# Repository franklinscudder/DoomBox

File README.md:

# DoomBox
 An insane glitchy analog fuzz pedal designed for bass guitar.

## Progress

- Designed circuit and selected components on breadboard.
- Made a stripboard prototype, added a level knob and LED indicator.
- Designed PCB found herein with added power filtering (easily bypassed if it turns out to be useless).
- Waiting for the PCBs to arrive to test final assembly.

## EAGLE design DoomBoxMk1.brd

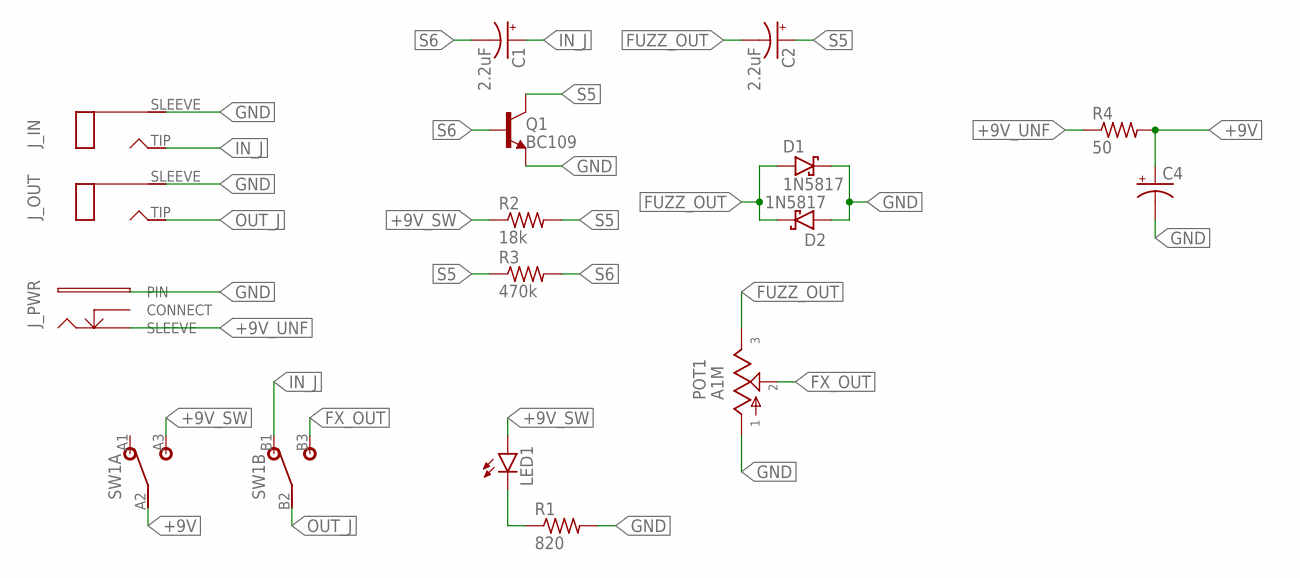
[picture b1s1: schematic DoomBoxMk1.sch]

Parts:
C1, C2: 2.2uF; 050_020_1
C4: 0802; 080_035_2
D1, D2: 1N5817; DO41-3
J_IN: MONO; MONO_JACK
J_OUT: MONO; MONO_JACK
J_PWR: DC; DC_POWER_JACK
LED1: LED5MM
POT1: A1M; 16MM-SQUARE
Q1: BC109; TO92-
R1: 820; R0207/3
R2: 18k; R0207/3
R3: 470k; R0207/3
R4: 50; R0207/3
SW1: DPDT

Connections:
+9V: C4.+, R4.2, SW1.A2 (2)
+9V_SW: LED1.A, R2.1, SW1.A3 (3)
+9V_UNF: J_PWR.SLEEVE, R4.1
FUZZ_OUT: C2.-, D1.A, D2.C, POT1.3
FX_OUT: POT1.2, SW1.B3 (3)
GND: C4.-, D1.C, D2.A, J_IN.SLEEVE, J_OUT.SLEEVE, J_PWR.PIN, POT1.1, Q1.1 (E), R1.2
IN_J: C1.+, J_IN.TIP, SW1.B1 (1)
unnamed: LED1.K (C), R1.1
OUT_J: J_OUT.TIP, SW1.B2 (2)
S5: C2.+, Q1.3 (C), R2.2, R3.1
S6: C1.-, Q1.2 (B), R3.2

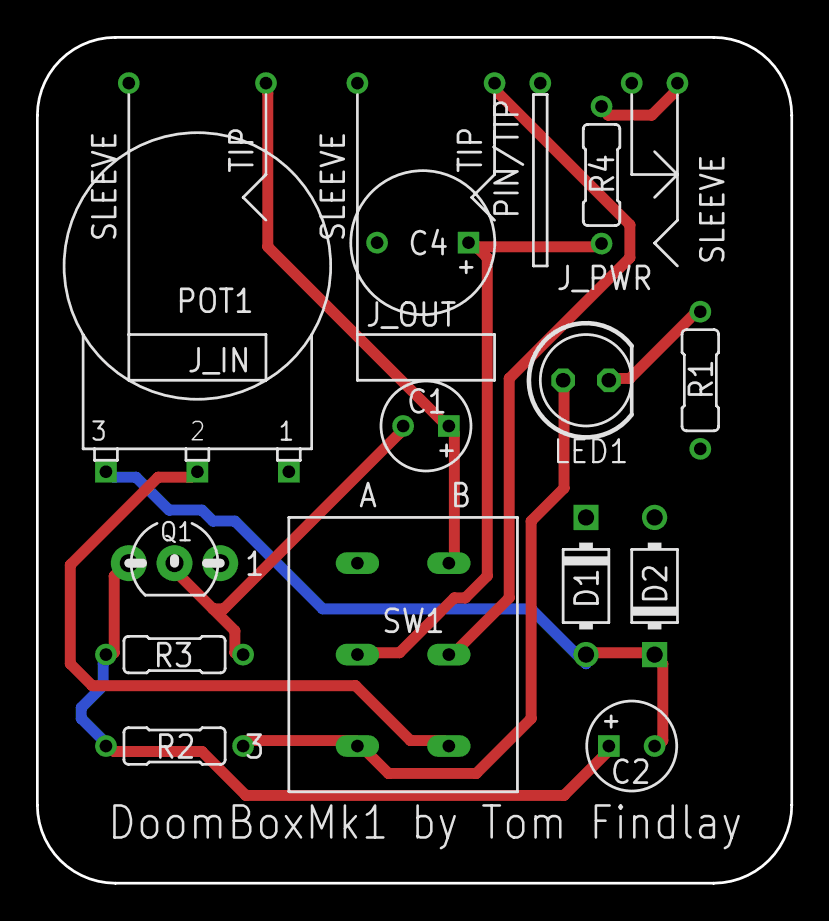
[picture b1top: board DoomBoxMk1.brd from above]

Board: 2 copper layers, 41.9 x 47.0 mm, 16 parts (0 on the bottom side), 11 nets.

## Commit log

2022-03-30 Added XR logo and filtered power version
2022-04-27 Added sample of bodged mk1 board and spice model
